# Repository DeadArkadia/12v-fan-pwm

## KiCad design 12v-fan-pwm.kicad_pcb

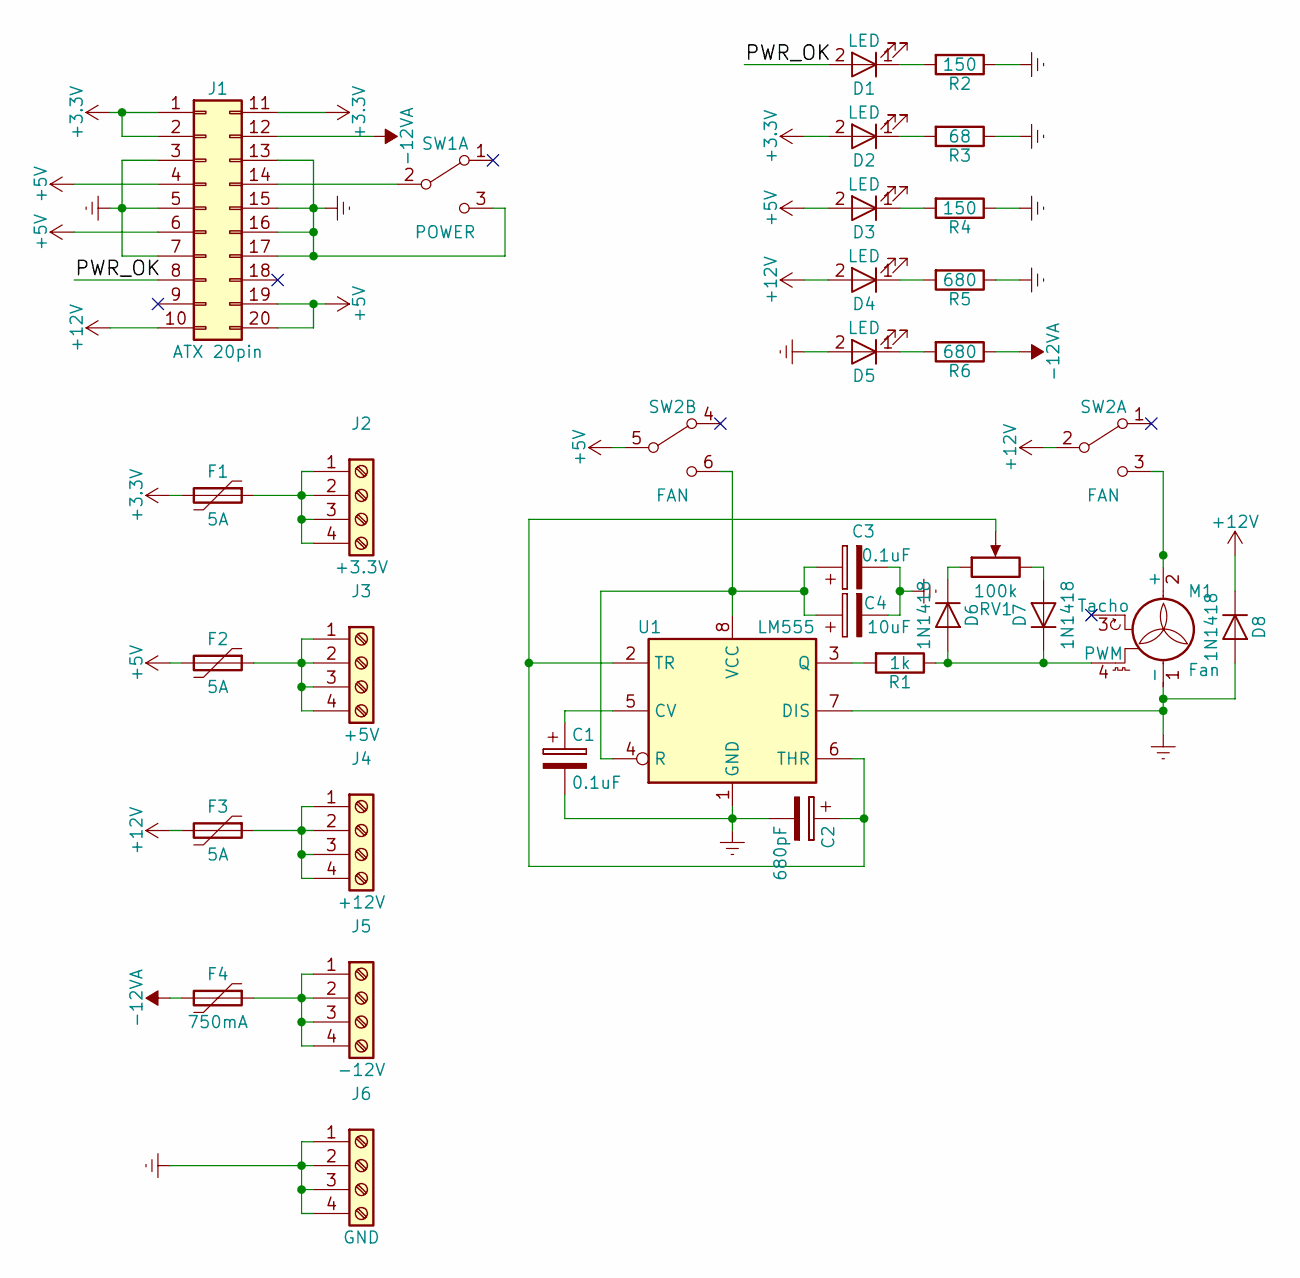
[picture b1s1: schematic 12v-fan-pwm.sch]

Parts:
C1, C3: 0.1uF; CP_Radial_D5.0mm_P2.50mm
C2: 680pF; CP_Radial_D5.0mm_P2.50mm
C4: 10uF; CP_Radial_D5.0mm_P2.50mm
D1, D2, D3, D4, D5: LED; LED_D5.0mm
D6, D7, D8: 1N1418; D_A-405_P7.62mm_Horizontal
F1, F2, F3: 5A; R_1812_4532Metric_Pad1.38x3.40mm_HandSolder
F4: 750mA; R_1206_3216Metric_Pad1.39x1.80mm_HandSolder
J1: ATX 20pin; Molex_MiniFit-JR-5569-20A2_2x10x4.20mm_Angled
J2: +3.3V; PhoenixContact_MSTBVA-G_04x5.00mm_Vertical
J3: +5V; PhoenixContact_MSTBVA-G_05x5.00mm_Vertical
J4: +12V; PhoenixContact_MSTBVA-G_05x5.00mm_Vertical
J5: -12V; PhoenixContact_MSTBVA-G_05x5.00mm_Vertical
J6: GND; PhoenixContact_MSTBVA-G_05x5.00mm_Vertical
M1: Fan; Molex_KK-6410-04_04x2.54mm_Straight
R1: 1k; R_Axial_DIN0207_L6.3mm_D2.5mm_P10.16mm_Horizontal
R2, R4: 150; R_Axial_DIN0207_L6.3mm_D2.5mm_P10.16mm_Horizontal
R3: 68; R_Axial_DIN0207_L6.3mm_D2.5mm_P10.16mm_Horizontal
R5, R6: 680; R_Axial_DIN0207_L6.3mm_D2.5mm_P10.16mm_Horizontal
RV1: 100k; Potentiometer_Triwood_RM-065
SW1: POWER; DIP-6_W7.62mm
SW2: FAN; DIP-6_W7.62mm
U1: LM555; DIP-8_W7.62mm

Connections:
+3V3: D2.2 (A), F1.2, J1.1, J1.2, J1.11
+5V: D3.2 (A), F2.2, J1.4, J1.6, J1.19, J1.20, SW2.5 (B)
+12V: D4.2 (A), D8.1 (K), F3.2, J1.10, SW2.2 (B)
-12VA: F4.2, J1.12, R6.1
/PWR_OK: D1.2 (A), J1.8
Earth: C1.2, C2.2, C3.2, C4.2, D5.2 (A), D8.2 (A), J1.3, J1.5, J1.7, J1.13, J1.15, J1.16, J1.17, J6.1, J6.2, J6.3, J6.4, M1.1 (-), R2.1, R3.1, R4.1, R5.1, SW1.3 (C), U1.1 (GND), U1.7 (DIS); also elsewhere on the board
unnamed: C1.1, U1.5 (CV)
unnamed: C2.1, RV1.2, U1.2 (TR), U1.6 (THR)
unnamed: C3.1, C4.1, SW2.6 (C), U1.4 (R), U1.8 (VCC)
unnamed: D1.1 (K), R2.2
unnamed: D2.1 (K), R3.2
unnamed: D3.1 (K), R4.2
unnamed: D4.1 (K), R5.2
unnamed: D5.1 (K), R6.2
unnamed: D6.1 (K), RV1.1
unnamed: D6.2 (A), D7.1 (K), M1.4 (PWM), R1.1
unnamed: D7.2 (A), RV1.3
unnamed: F1.1, J2.1, J2.2, J2.3, J2.4
unnamed: F2.1, J3.1, J3.2, J3.3, J3.4
unnamed: F3.1, J4.1, J4.2, J4.3, J4.4
unnamed: F4.1, J5.1, J5.2, J5.3, J5.4
unnamed: J1.14, SW1.2 (B)
unnamed: M1.2 (+), SW2.3 (C)
unnamed: R1.2, U1.3 (Q)

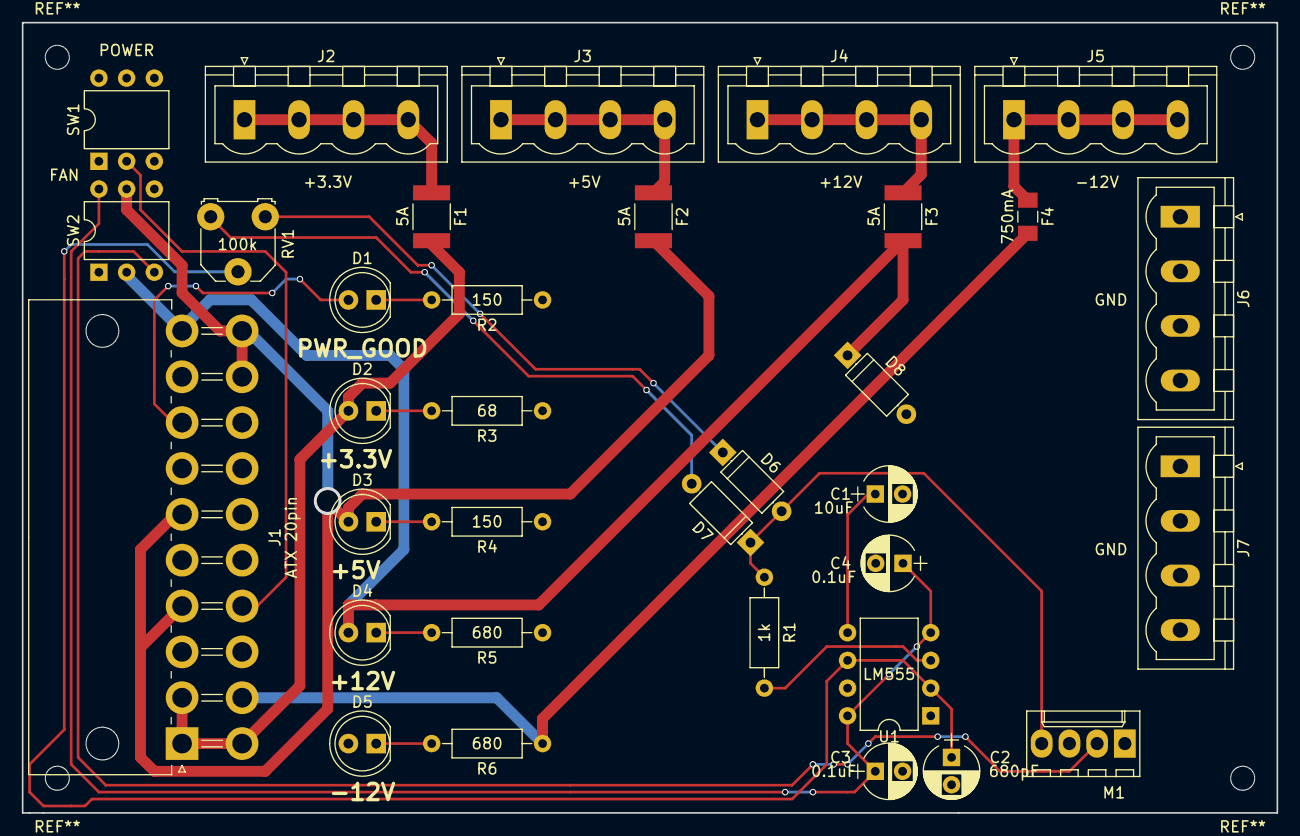
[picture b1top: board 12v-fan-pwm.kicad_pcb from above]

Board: 2 copper layers, 114.9 x 72.4 mm, 34 parts (0 on the bottom side), 24 nets.

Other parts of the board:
J7: GND; PhoenixContact_MSTBVA-G_04x5.00mm_Vertical

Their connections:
Earth: J7.1, J7.2, J7.3, J7.4; also elsewhere on the board

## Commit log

2018-05-10 final pcb
    laid out and exported, ready to print
